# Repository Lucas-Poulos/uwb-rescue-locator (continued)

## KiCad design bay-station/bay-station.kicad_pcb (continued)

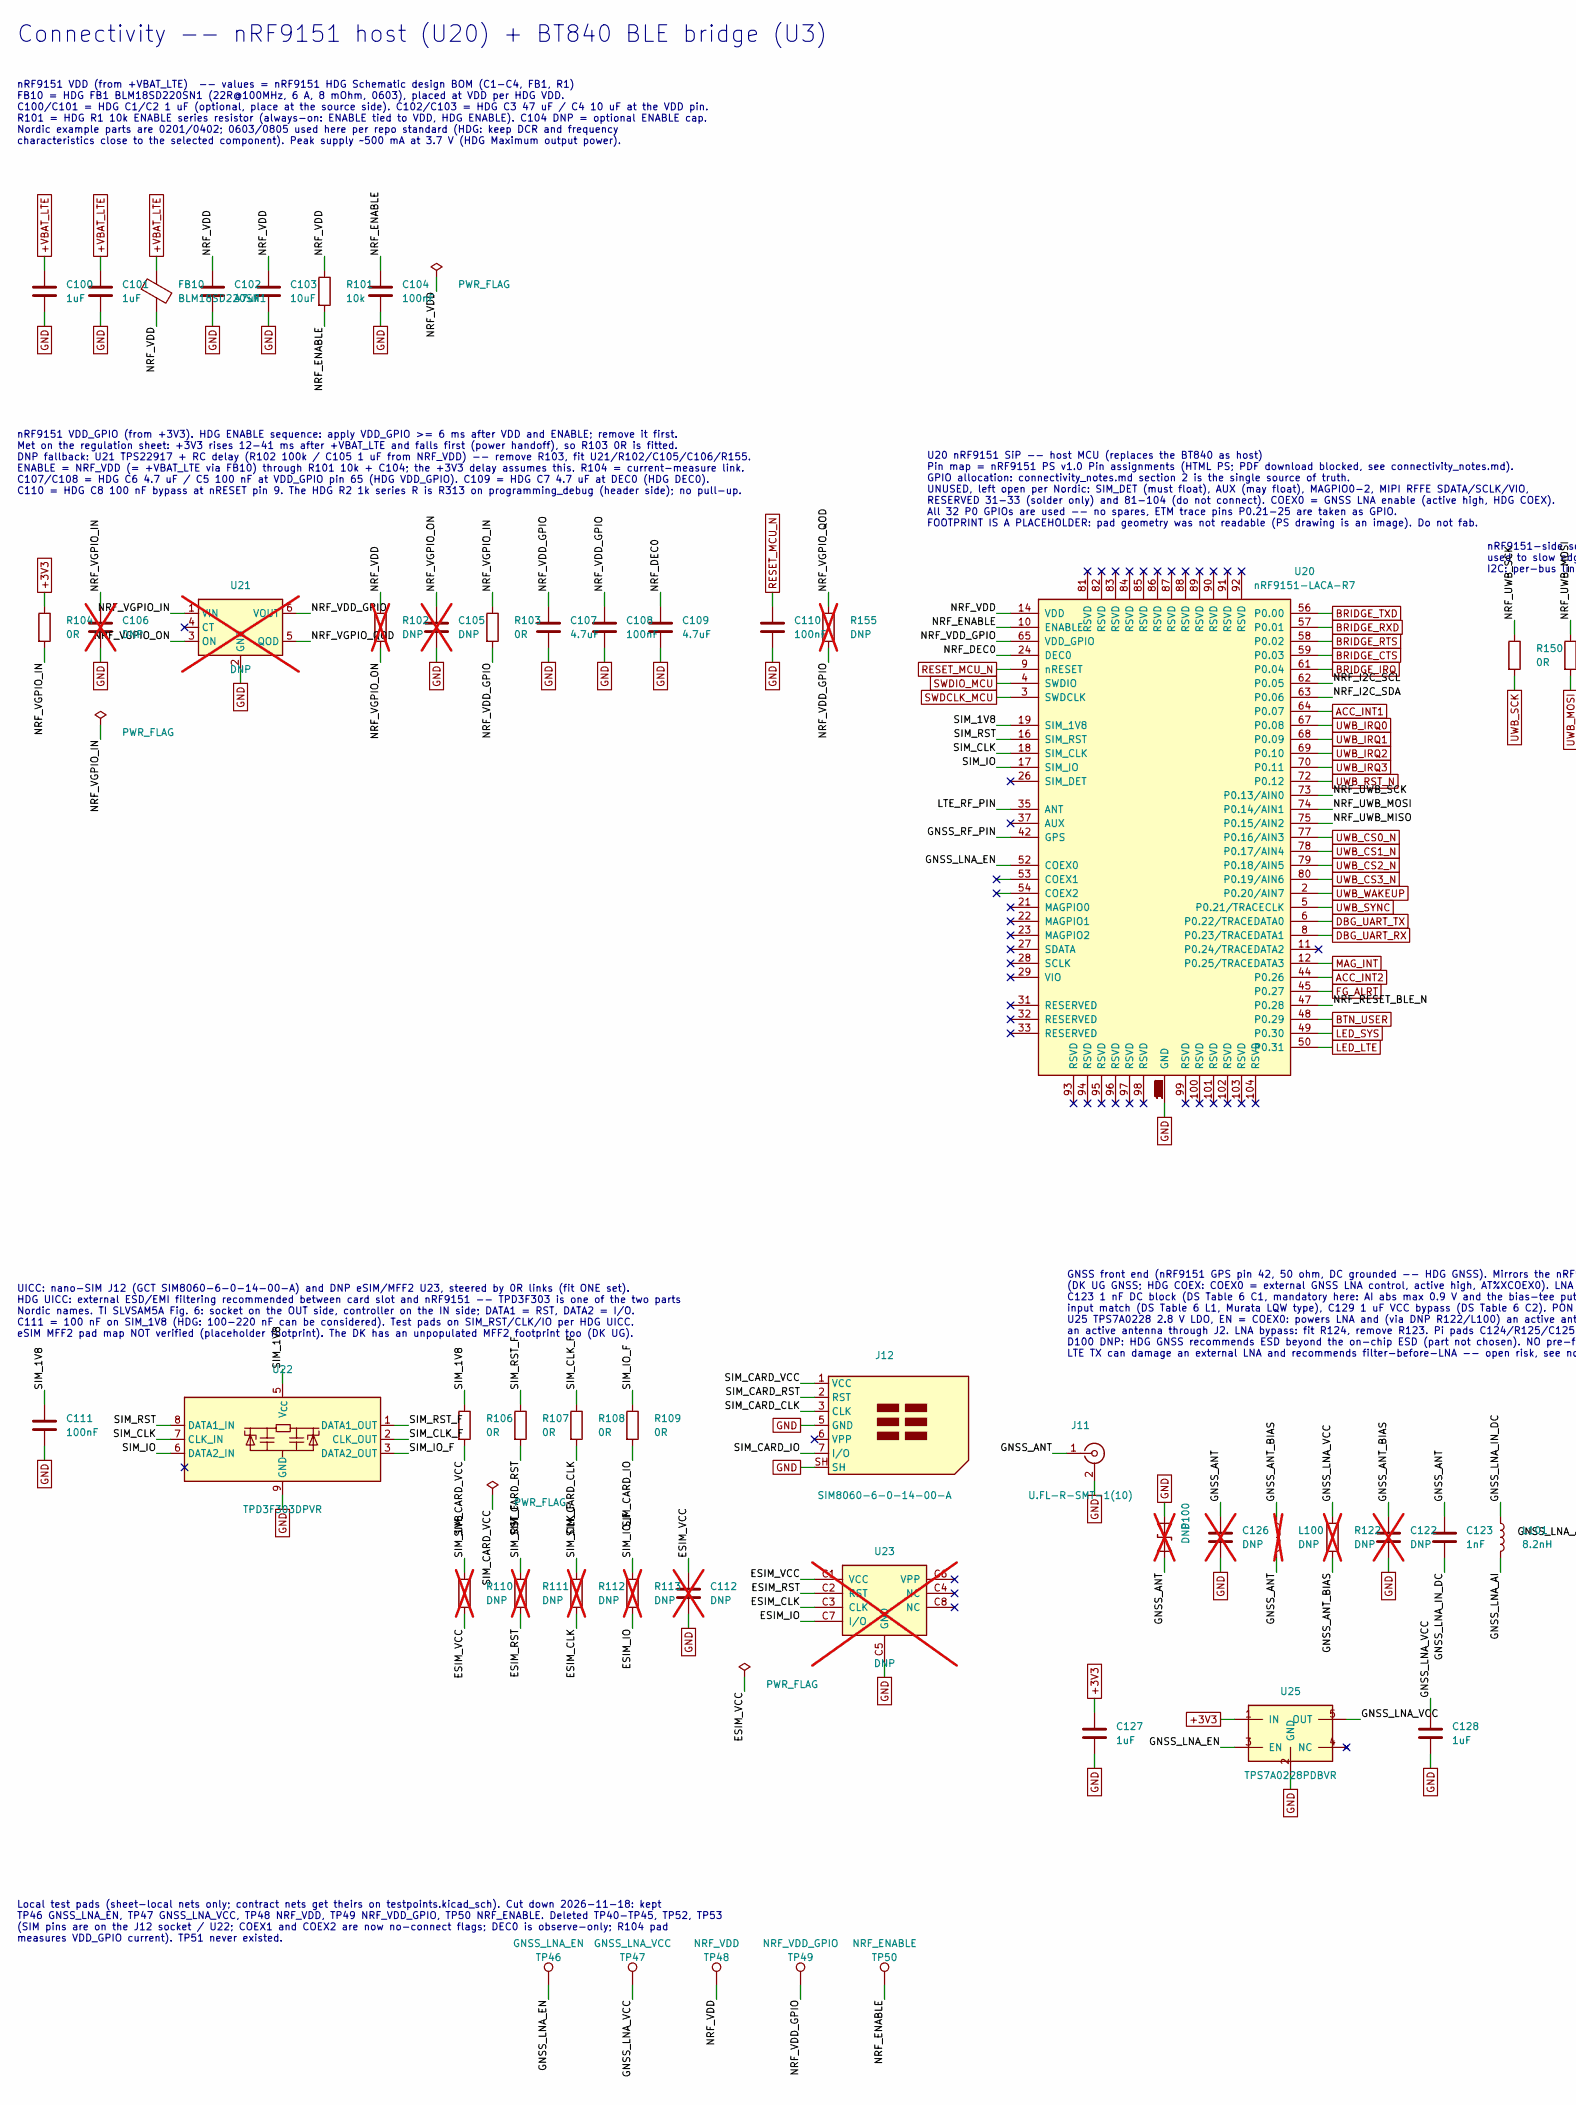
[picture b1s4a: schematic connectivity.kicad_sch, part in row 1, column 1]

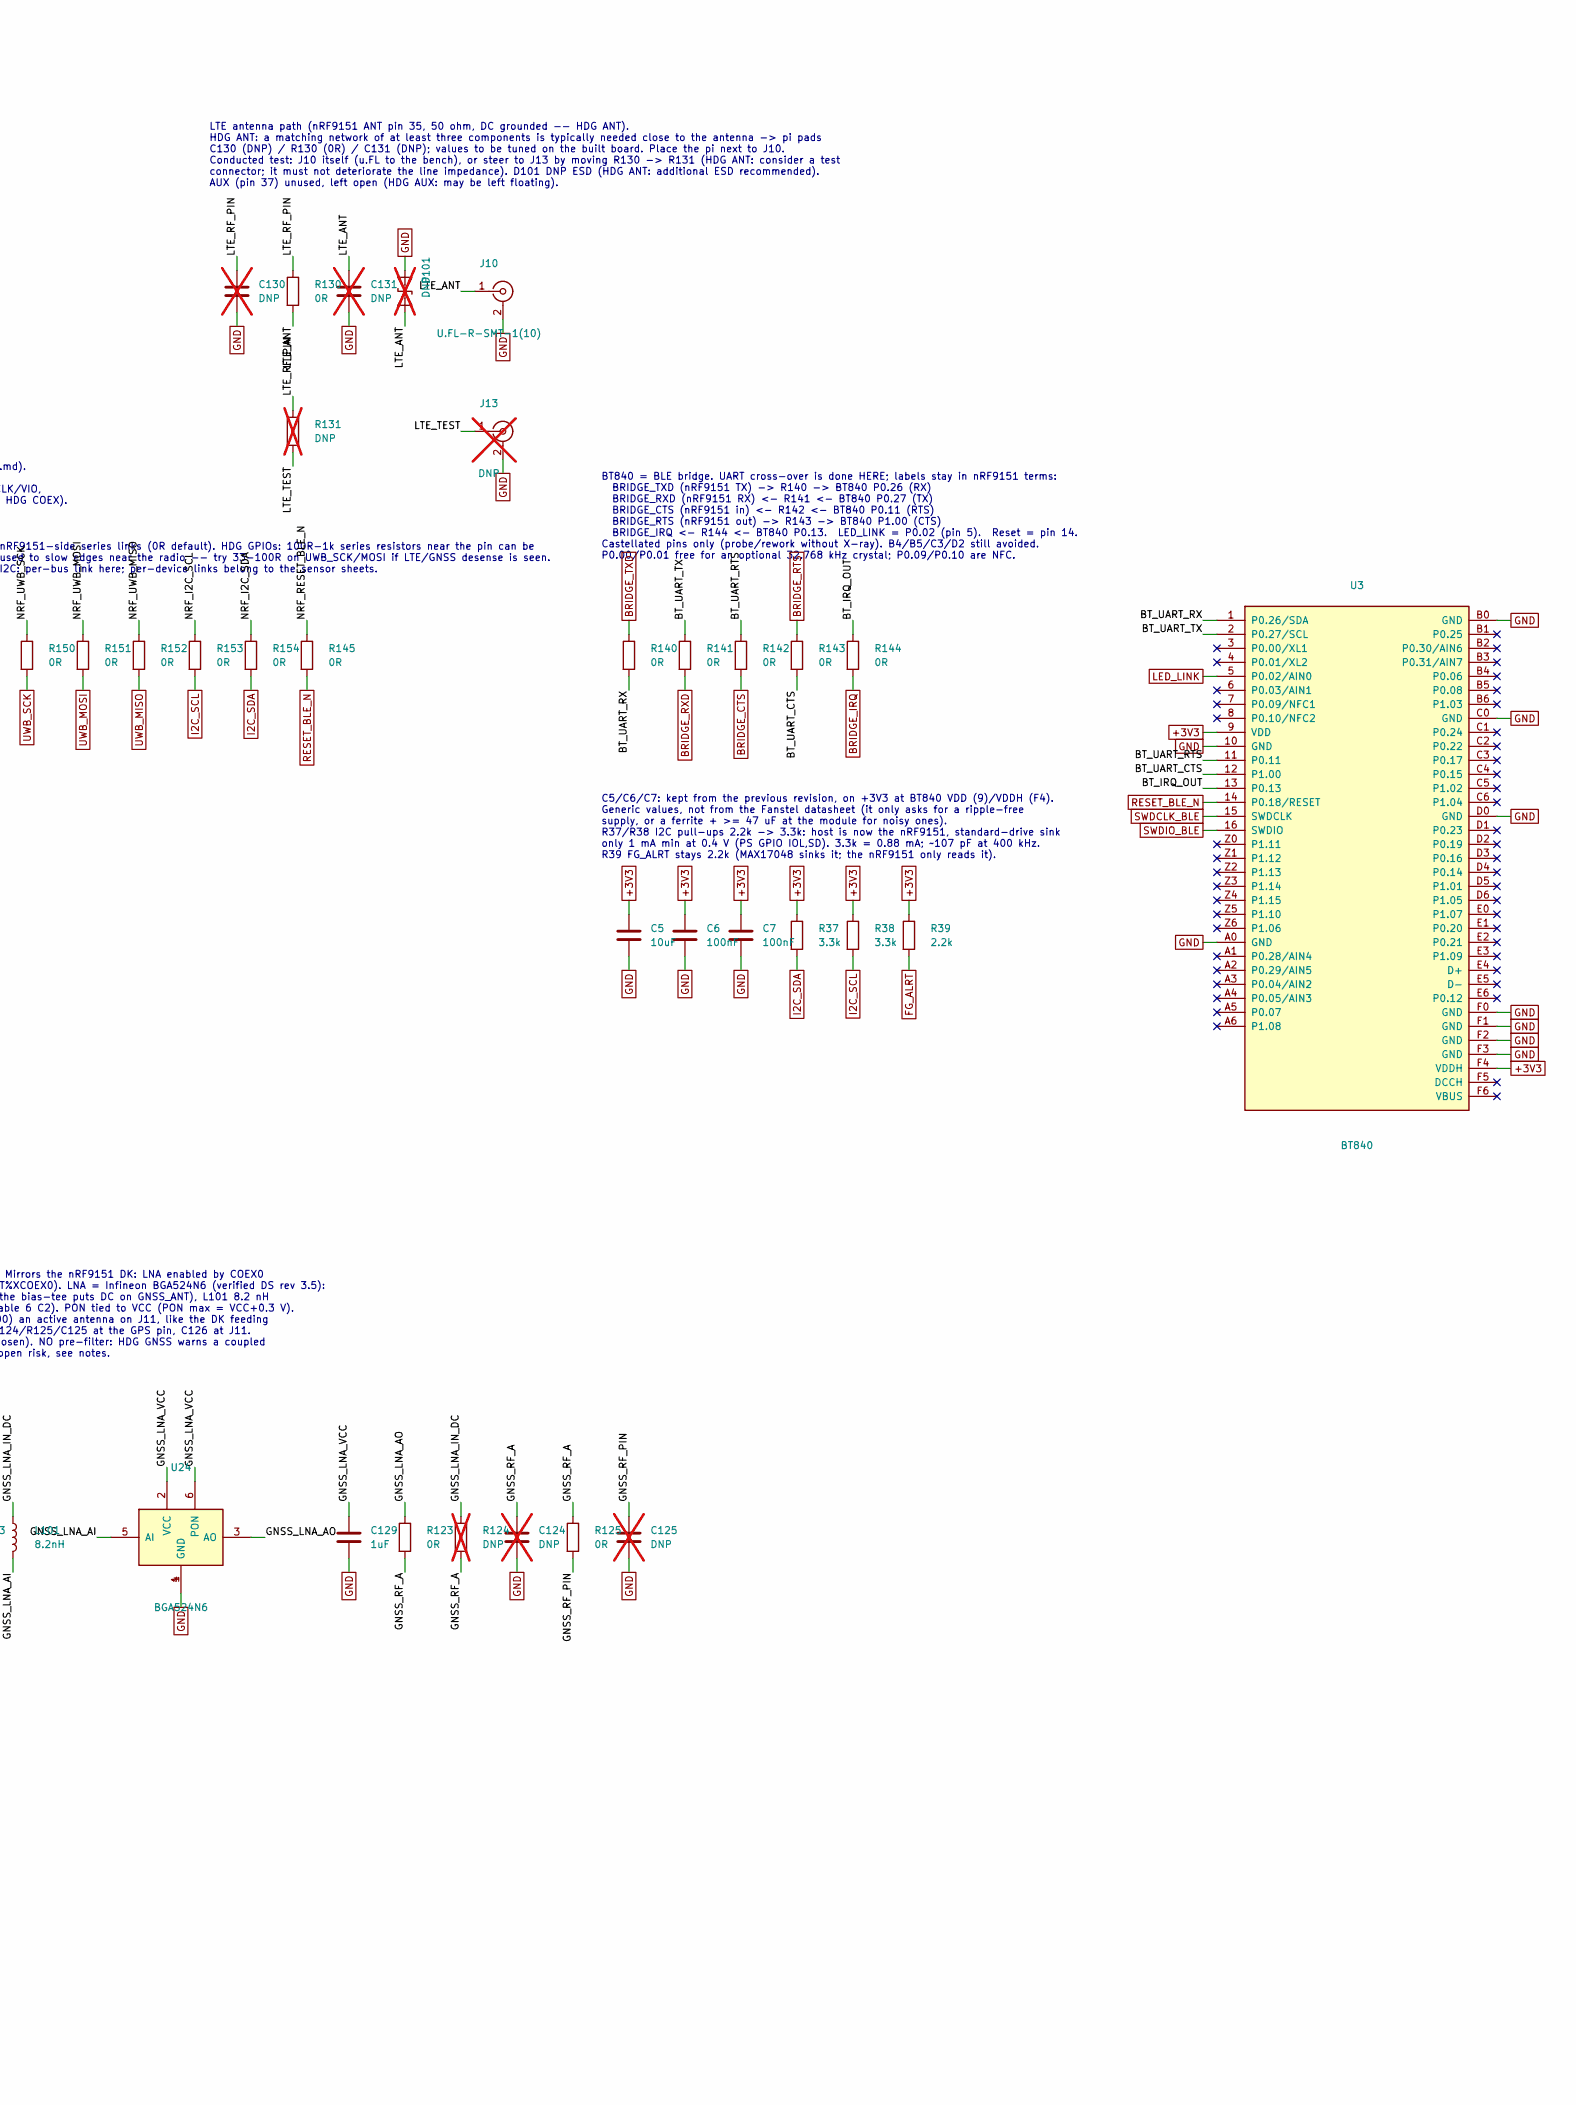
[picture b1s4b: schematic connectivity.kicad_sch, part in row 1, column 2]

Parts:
C5, C103: 10uF; C_0603_1608Metric
C6, C7, C104, C108, C110, C111: 100nF; C_0603_1608Metric
C100, C101, C127, C128, C129: 1uF; C_0603_1608Metric
C102: 47uF; C_0805_2012Metric
C105, C106, C112: DNP; C_0603_1608Metric; not fitted
C107, C109: 4.7uF; C_0603_1608Metric
C122, C124, C125, C126, C130, C131: DNP; C_0402_1005Metric; not fitted
C123: 1nF; C_0402_1005Metric
D100, D101: DNP; D_0402_1005Metric; not fitted
FB10: BLM18SD220SN1; L_0603_1608Metric
J10, J11: U.FL-R-SMT-1(10); U.FL_Hirose_U.FL-R-SMT-1_Vertical
J12: SIM8060-6-0-14-00-A; nanoSIM_GCT_SIM8060-6-0-14-00
J13: DNP; U.FL_Hirose_U.FL-R-SMT-1_Vertical; not fitted
L100: DNP; L_0402_1005Metric; not fitted
L101: 8.2nH; L_0402_1005Metric
R37, R38: 3.3k; R_0603_1608Metric
R39: 2.2k; R_0603_1608Metric
R101: 10k; R_0603_1608Metric
R102, R110, R111, R112, R113, R122, R155: DNP; R_0603_1608Metric; not fitted
R103, R104, R106, R107, R108, R109, R140, R141, R142, R143, R144, R145, R150, R151, R152, R153, R154: 0R; R_0603_1608Metric
R123, R125, R130: 0R; R_0402_1005Metric
R124, R131: DNP; R_0402_1005Metric; not fitted
TP46: GNSS_LNA_EN; TestPoint_Pad_D1.0mm
TP47: GNSS_LNA_VCC; TestPoint_Pad_D1.0mm
TP48: NRF_VDD; TestPoint_Pad_D1.0mm
TP49: NRF_VDD_GPIO; TestPoint_Pad_D1.0mm
TP50: NRF_ENABLE; TestPoint_Pad_D1.0mm
U3: BT840; Fanstel_BT840_Module_14x16mm_16Cast_49LGA
U20: nRF9151-LACA-R7; Nordic_nRF9151_LGA-113_12.1x11.1mm_P0.5mm
U21: DNP; SOT-23-6; not fitted
U22: TPD3F303DPVR; Texas_R-PUSON-N8_USON-8-1EP_1.6x2.1mm_P0.5mm_EP0.4x1.7mm
U23: DNP; eSIM_MFF2_PLACEHOLDER; not fitted
U24: BGA524N6; Infineon_TSNP-6-2_0.7x1.1mm_P0.4mm
U25: TPS7A0228PDBVR; SOT-23-5

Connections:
+3V3: C5.1, C6.1, C7.1, C127.1, R37.1, R38.1, R39.1, R104.1, U3.9 (VDD), U3.F4 (VDDH), U25.1 (IN); also elsewhere on the board
+VBAT_LTE: C100.1, C101.1, FB10.1; also elsewhere on the board
/Connectivity/BT_IRQ_OUT: R144.1, U3.13 (P0.13)
/Connectivity/BT_UART_CTS: R143.2, U3.12 (P1.00)
/Connectivity/BT_UART_RTS: R142.1, U3.11 (P0.11)
/Connectivity/BT_UART_RX: R140.2, U3.1 (P0.26/SDA)
/Connectivity/BT_UART_TX: R141.1, U3.2 (P0.27/SCL)
/Connectivity/ESIM_CLK: R112.2, U23.C3 (CLK)
/Connectivity/ESIM_IO: R113.2, U23.C7 (I/O)
/Connectivity/ESIM_RST: R111.2, U23.C2 (RST)
/Connectivity/ESIM_VCC: C112.1, R110.2, U23.C1 (VCC)
/Connectivity/GNSS_ANT: C123.1, C126.1, D100.1 (A1), J11.1 (In), L100.2
/Connectivity/GNSS_ANT_BIAS: C122.1, L100.1, R122.2
/Connectivity/GNSS_LNA_AI: L101.2, U24.5 (AI)
/Connectivity/GNSS_LNA_AO: R123.1, U24.3 (AO)
/Connectivity/GNSS_LNA_EN: TP46.1 (1_1), U20.52 (COEX0), U25.3 (EN)
/Connectivity/GNSS_LNA_IN_DC: C123.2, L101.1, R124.1
/Connectivity/GNSS_LNA_VCC: C128.1, C129.1, R122.1, TP47.1 (1_1), U24.2 (VCC), U24.6 (PON), U25.5 (OUT)
/Connectivity/GNSS_RF_A: C124.1, R123.2, R124.2, R125.1
/Connectivity/GNSS_RF_PIN: C125.1, R125.2, U20.42 (GPS)
/Connectivity/LTE_ANT: C131.1, D101.1 (A1), J10.1 (In), R130.2
/Connectivity/LTE_RF_PIN: C130.1, R130.1, R131.1, U20.35 (ANT)
/Connectivity/LTE_TEST: J13.1 (In), R131.2
/Connectivity/NRF_DEC0: C109.1, U20.24 (DEC0)
/Connectivity/NRF_ENABLE: C104.1, R101.2, TP50.1 (1_1), U20.10 (ENABLE)
/Connectivity/NRF_I2C_SCL: R153.1, U20.62 (P0.05)
/Connectivity/NRF_I2C_SDA: R154.1, U20.63 (P0.06)
/Connectivity/NRF_RESET_BLE_N: R145.1, U20.47 (P0.28)
/Connectivity/NRF_UWB_MISO: R152.1, U20.75 (P0.15/AIN2)
/Connectivity/NRF_UWB_MOSI: R151.1, U20.74 (P0.14/AIN1)
/Connectivity/NRF_UWB_SCK: R150.1, U20.73 (P0.13/AIN0)
/Connectivity/NRF_VDD: C102.1, C103.1, FB10.2, R101.1, R102.1, TP48.1 (1_1), U20.14 (VDD)
/Connectivity/NRF_VDD_GPIO: C107.1, C108.1, R103.2, R155.2, TP49.1 (1_1), U20.65 (VDD_GPIO), U21.6 (VOUT)
/Connectivity/NRF_VGPIO_IN: C106.1, R103.1, R104.2, U21.1 (VIN)
/Connectivity/NRF_VGPIO_ON: C105.1, R102.2, U21.3 (ON)
/Connectivity/NRF_VGPIO_QOD: R155.1, U21.5 (QOD)
/Connectivity/SIM_1V8: C111.1, R106.1, R110.1, U20.19 (SIM_1V8), U22.5 (V_{CC})
/Connectivity/SIM_CARD_CLK: J12.3 (CLK), R108.2
/Connectivity/SIM_CARD_IO: J12.7 (I/O), R109.2
/Connectivity/SIM_CARD_RST: J12.2 (RST), R107.2
/Connectivity/SIM_CARD_VCC: J12.1 (VCC), R106.2
/Connectivity/SIM_CLK: U20.18 (SIM_CLK), U22.7 (CLK_IN)
/Connectivity/SIM_CLK_F: R108.1, R112.1, U22.2 (CLK_OUT)
/Connectivity/SIM_IO: U20.17 (SIM_IO), U22.6 (DATA2_IN)
/Connectivity/SIM_IO_F: R109.1, R113.1, U22.3 (DATA2_OUT)
/Connectivity/SIM_RST: U20.16 (SIM_RST), U22.8 (DATA1_IN)
/Connectivity/SIM_RST_F: R107.1, R111.1, U22.1 (DATA1_OUT)
ACC_INT1: U20.64 (P0.07); also elsewhere on the board
ACC_INT2: U20.44 (P0.26); also elsewhere on the board
BRIDGE_CTS: R142.2, U20.59 (P0.03); also elsewhere on the board
BRIDGE_IRQ: R144.2, U20.61 (P0.04); also elsewhere on the board
BRIDGE_RTS: R143.1, U20.58 (P0.02); also elsewhere on the board
BRIDGE_RXD: R141.2, U20.57 (P0.01); also elsewhere on the board
BRIDGE_TXD: R140.1, U20.56 (P0.00); also elsewhere on the board
BTN_USER: U20.48 (P0.29); also elsewhere on the board
DBG_UART_RX: U20.8 (P0.23/TRACEDATA1); also elsewhere on the board
DBG_UART_TX: U20.6 (P0.22/TRACEDATA0); also elsewhere on the board
FG_ALRT: R39.2, U20.45 (P0.27); also elsewhere on the board
GND: C5.2, C6.2, C7.2, C100.2, C101.2, C102.2, C103.2, C104.2, C105.2, C106.2, C107.2, C108.2, C109.2, C110.2, C111.2, C112.2, C122.2, C124.2, C125.2, C126.2, C127.2, C128.2, C129.2, C130.2, C131.2, D100.2 (A2), D101.2 (A2), J10.2 (Ext), J11.2 (Ext), J12.5 (GND), J12.SH, J13.2 (Ext), U3.10 (GND), U3.A0 (GND), U3.B0 (GND), U3.C0 (GND), U3.D0 (GND), U3.F0 (GND), U3.F1 (GND), U3.F2 (GND), U3.F3 (GND), U20.1 (GND), U20.7 (GND), U20.13 (GND), U20.15 (GND), U20.20 (GND), U20.25 (GND), U20.30 (GND), U20.34 (GND), U20.36 (GND), U20.38 (GND), U20.39 (GND), U20.40 (GND), U20.41 (GND), U20.43 (GND), U20.46 (GND), U20.51 (GND), U20.55 (GND), U20.60 (GND), U20.66 (GND), U20.71 (GND), U20.76 (GND), U20.105 (GND), U20.106 (GND), U20.107 (GND), U20.108 (GND), U20.109 (GND), U20.110 (GND), U20.111 (GND), U20.112 (GND), U20.113 (GND), U21.2 (GND), U22.9 (GND), U23.C5 (GND), U24.1 (GND), U24.4 (GND), U25.2 (GND); also elsewhere on the board
I2C_SCL: R38.2, R153.2; also elsewhere on the board
I2C_SDA: R37.2, R154.2; also elsewhere on the board
LED_LINK: U3.5 (P0.02/AIN0); also elsewhere on the board
LED_LTE: U20.50 (P0.31); also elsewhere on the board
LED_SYS: U20.49 (P0.30); also elsewhere on the board
MAG_INT: U20.12 (P0.25/TRACEDATA3); also elsewhere on the board
RESET_BLE_N: R145.2, U3.14 (P0.18/RESET); also elsewhere on the board
RESET_MCU_N: C110.1, U20.9 (nRESET); also elsewhere on the board
SWDCLK_BLE: U3.15 (SWDCLK); also elsewhere on the board
SWDCLK_MCU: U20.3 (SWDCLK); also elsewhere on the board
SWDIO_BLE: U3.16 (SWDIO); also elsewhere on the board
SWDIO_MCU: U20.4 (SWDIO); also elsewhere on the board
UWB_CS0_N: U20.77 (P0.16/AIN3); also elsewhere on the board
UWB_CS1_N: U20.78 (P0.17/AIN4); also elsewhere on the board
UWB_CS2_N: U20.79 (P0.18/AIN5); also elsewhere on the board
UWB_CS3_N: U20.80 (P0.19/AIN6); also elsewhere on the board
UWB_IRQ0: U20.67 (P0.08); also elsewhere on the board
UWB_IRQ1: U20.68 (P0.09); also elsewhere on the board
UWB_IRQ2: U20.69 (P0.10); also elsewhere on the board
UWB_IRQ3: U20.70 (P0.11); also elsewhere on the board
UWB_MISO: R152.2; also elsewhere on the board
UWB_MOSI: R151.2; also elsewhere on the board
UWB_RST_N: U20.72 (P0.12); also elsewhere on the board
UWB_SCK: R150.2; also elsewhere on the board
UWB_SYNC: U20.5 (P0.21/TRACECLK); also elsewhere on the board
UWB_WAKEUP: U20.2 (P0.20/AIN7); also elsewhere on the board

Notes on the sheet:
U20 nRF9151 SiP -- host MCU (replaces the BT840 as host) Pin map = nRF9151 PS v1.0 Pin assignments (HTML PS; PDF download blocked, see connectivity_notes.md). GPIO allocation: connectivity_notes.md section 2 is the single source of truth. UNUSED, left open per Nordic: SIM_DET (must float), AUX (may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
LTE antenna path (nRF9151 ANT pin 35, 50 ohm, DC grounded -- HDG ANT). HDG ANT: a matching network of at least three components is typically needed close to the antenna -> pi pads C130 (DNP) / R130 (0R) / C131 (DNP); values to be tuned on the built board. Place the pi next to J10. Conducted test: J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
Connectivity -- nRF9151 host (U20) + BT840 BLE bridge (U3)
C5/C6/C7: kept from the previous revision, on +3V3 at BT840 VDD (9)/VDDH (F4). Generic values, not from the Fanstel datasheet (it only asks for a ripple-free supply, or a ferrite + >= 47 uF at the module for noisy ones). R37/R38 I2C pull-ups 2.2k -> 3.3k: host is now the nRF9151, standard-drive sin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
Local test pads (sheet-local nets only; contract nets get theirs on testpoints.kicad_sch). Cut down 2026-11-18: kept TP46 GNSS_LNA_EN, TP47 GNSS_LNA_VCC, TP48 NRF_VDD, TP49 NRF_VDD_GPIO, TP50 NRF_ENABLE. Deleted TP40-TP45, TP52, TP53 (SIM pins are on the J12 socket / U22; COEX1 and COEX2 are now no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
GNSS front end (nRF9151 GPS pin 42, 50 ohm, DC grounded -- HDG GNSS). Mirrors the nRF9151 DK: LNA enabled by COEX0 (DK UG GNSS; HDG COEX: COEX0 = external GNSS LNA control, active high, AT%XCOEX0). LNA = Infineon BGA524N6 (verified DS rev 3.5): C123 1 nF DC block (DS Table 6 C1, mandatory here: AI 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
nRF9151 VDD_GPIO (from +3V3). HDG ENABLE sequence: apply VDD_GPIO >= 6 ms after VDD and ENABLE; remove it first. Met on the regulation sheet: +3V3 rises 12-41 ms after +VBAT_LTE and falls first (power handoff), so R103 0R is fitted. DNP fallback: U21 TPS22917 + RC delay (R102 100k / C105 1 uF from 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
UICC: nano-SIM J12 (GCT SIM8060-6-0-14-00-A) and DNP eSIM/MFF2 U23, steered by 0R links (fit ONE set). HDG UICC: external ESD/EMI filtering recommended between card slot and nRF9151 -- TPD3F303 is one of the two parts Nordic names. TI SLVSAM5A Fig. 6: socket on the OUT side, controller on the IN si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
nRF9151 VDD (from +VBAT_LTE) -- values = nRF9151 HDG Schematic design BOM (C1-C4, FB1, R1) FB10 = HDG FB1 BLM18SD220SN1 (22R@100MHz, 6 A, 8 mOhm, 0603), placed at VDD per HDG VDD. C100/C101 = HDG C1/C2 1 uF (optional, place at the source side). C102/C103 = HDG C3 47 uF / C4 10 uF at the VDD pin. R1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
nRF9151-side series links (0R default). HDG GPIOs: 100R-1k series resistors near the pin can be used to slow edges near the radio -- try 33-100R on UWB_SCK/MOSI if LTE/GNSS desense is seen. I2C: per-bus link here; per-device links belong to the sensor sheets.
BT840 = BLE bridge. UART cross-over is done HERE; labels stay in nRF9151 terms: BRIDGE_TXD (nRF9151 TX) -> R140 -> BT840 P0.26 (RX) BRIDGE_RXD (nRF9151 RX) <- R141 <- BT840 P0.27 (TX) BRIDGE_CTS (nRF9151 in) <- R142 <- BT840 P0.11 (RTS) BRIDGE_RTS (nRF9151 out) -> R143 -> BT840 P1.00 (CTS) BRIDGE_I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

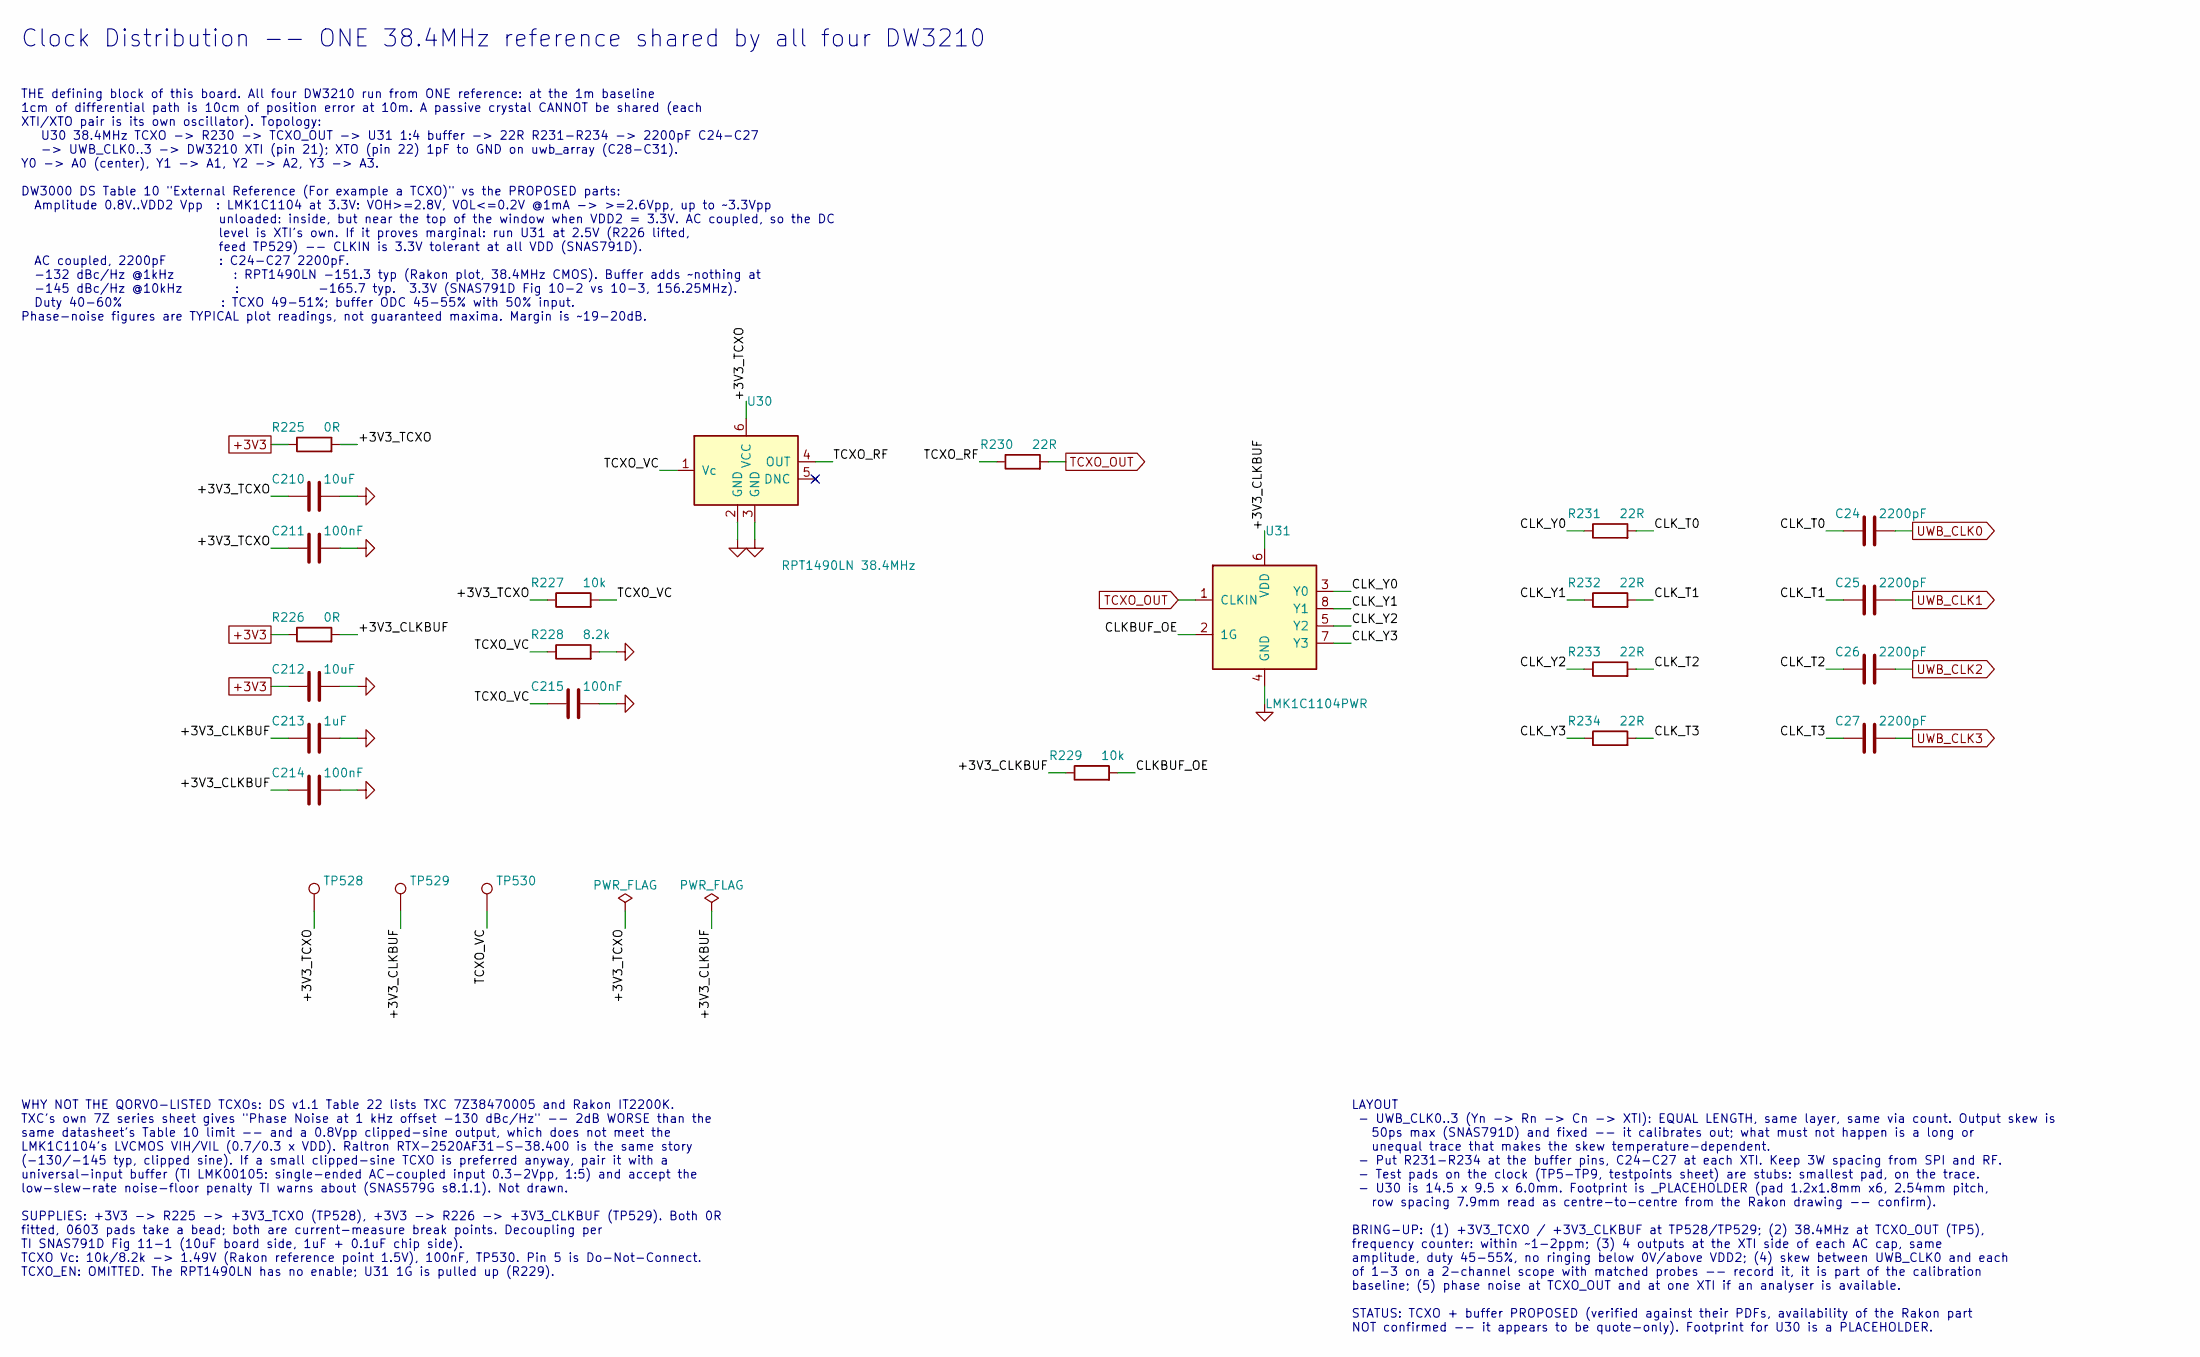
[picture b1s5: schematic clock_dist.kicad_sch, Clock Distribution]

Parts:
C24, C25, C26, C27: 2200pF; C_0603_1608Metric
C210, C212: 10uF; C_0603_1608Metric
C211, C214, C215: 100nF; C_0603_1608Metric
C213: 1uF; C_0603_1608Metric
R225, R226: 0R; R_0603_1608Metric
R227, R229: 10k; R_0603_1608Metric
R228: 8.2k; R_0603_1608Metric
R230, R231, R232, R233, R234: 22R; R_0603_1608Metric
TP528: +3V3_TCXO; TestPoint_Pad_D1.0mm
TP529: +3V3_CLKBUF; TestPoint_Pad_D1.0mm
TP530: TCXO_VC; TestPoint_Pad_D1.0mm
U30: RPT1490LN 38.4MHz; Rakon_RPT1490LN_14.5x9.5mm_PLACEHOLDER; MPN RPT1490LN (38.4MHz; ordering code TBC)
U31: LMK1C1104PWR; TSSOP-8_4.4x3mm_P0.65mm; MPN LMK1C1104PWR

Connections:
+3V3: C212.1, R225.1, R226.1; also elsewhere on the board
/Clock Distribution/+3V3_CLKBUF: C213.1, C214.1, R226.2, R229.1, TP529.1 (1_1), U31.6 (VDD)
/Clock Distribution/+3V3_TCXO: C210.1, C211.1, R225.2, R227.1, TP528.1 (1_1), U30.6 (VCC)
/Clock Distribution/CLKBUF_OE: R229.2, U31.2 (1G)
/Clock Distribution/CLK_T0: C24.1, R231.2
/Clock Distribution/CLK_T1: C25.1, R232.2
/Clock Distribution/CLK_T2: C26.1, R233.2
/Clock Distribution/CLK_T3: C27.1, R234.2
/Clock Distribution/CLK_Y0: R231.1, U31.3 (Y0)
/Clock Distribution/CLK_Y1: R232.1, U31.8 (Y1)
/Clock Distribution/CLK_Y2: R233.1, U31.5 (Y2)
/Clock Distribution/CLK_Y3: R234.1, U31.7 (Y3)
/Clock Distribution/TCXO_RF: R230.1, U30.4 (OUT)
/Clock Distribution/TCXO_VC: C215.1, R227.2, R228.1, TP530.1 (1_1), U30.1 (Vc)
GND: C210.2, C211.2, C212.2, C213.2, C214.2, C215.2, R228.2, U30.2 (GND), U30.3 (GND), U31.4 (GND); also elsewhere on the board
TCXO_OUT: R230.2, U31.1 (CLKIN); also elsewhere on the board
UWB_CLK0: C24.2; also elsewhere on the board
UWB_CLK1: C25.2; also elsewhere on the board
UWB_CLK2: C26.2; also elsewhere on the board
UWB_CLK3: C27.2; also elsewhere on the board

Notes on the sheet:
LAYOUT - UWB_CLK0..3 (Yn -> Rn -> Cn -> XTI): EQUAL LENGTH, same layer, same via count. Output skew is 50ps max (SNAS791D) and fixed -- it calibrates out; what must not happen is a long or unequal trace that makes the skew temperature-dependent. - Put R231-R234 at the buffer pins, C24-C27 at each X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
WHY NOT THE QORVO-LISTED TCXOs: DS v1.1 Table 22 lists TXC 7Z38470005 and Rakon IT2200K. TXC's own 7Z series sheet gives "Phase Noise at 1 kHz offset -130 dBc/Hz" -- 2dB WORSE than the same datasheet's Table 10 limit -- and a 0.8Vpp clipped-sine output, which does not meet the LMK1C1104's LVCMOS VI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
Clock Distribution -- ONE 38.4MHz reference shared by all four DW3210
THE defining block of this board. All four DW3210 run from ONE reference: at the 1m baseline 1cm of differential path is 10cm of position error at 10m. A passive crystal CANNOT be shared (each XTI/XTO pair is its own oscillator). Topology: U30 38.4MHz TCXO -> R230 -> TCXO_OUT -> U31 1:4 buffer -> 2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
